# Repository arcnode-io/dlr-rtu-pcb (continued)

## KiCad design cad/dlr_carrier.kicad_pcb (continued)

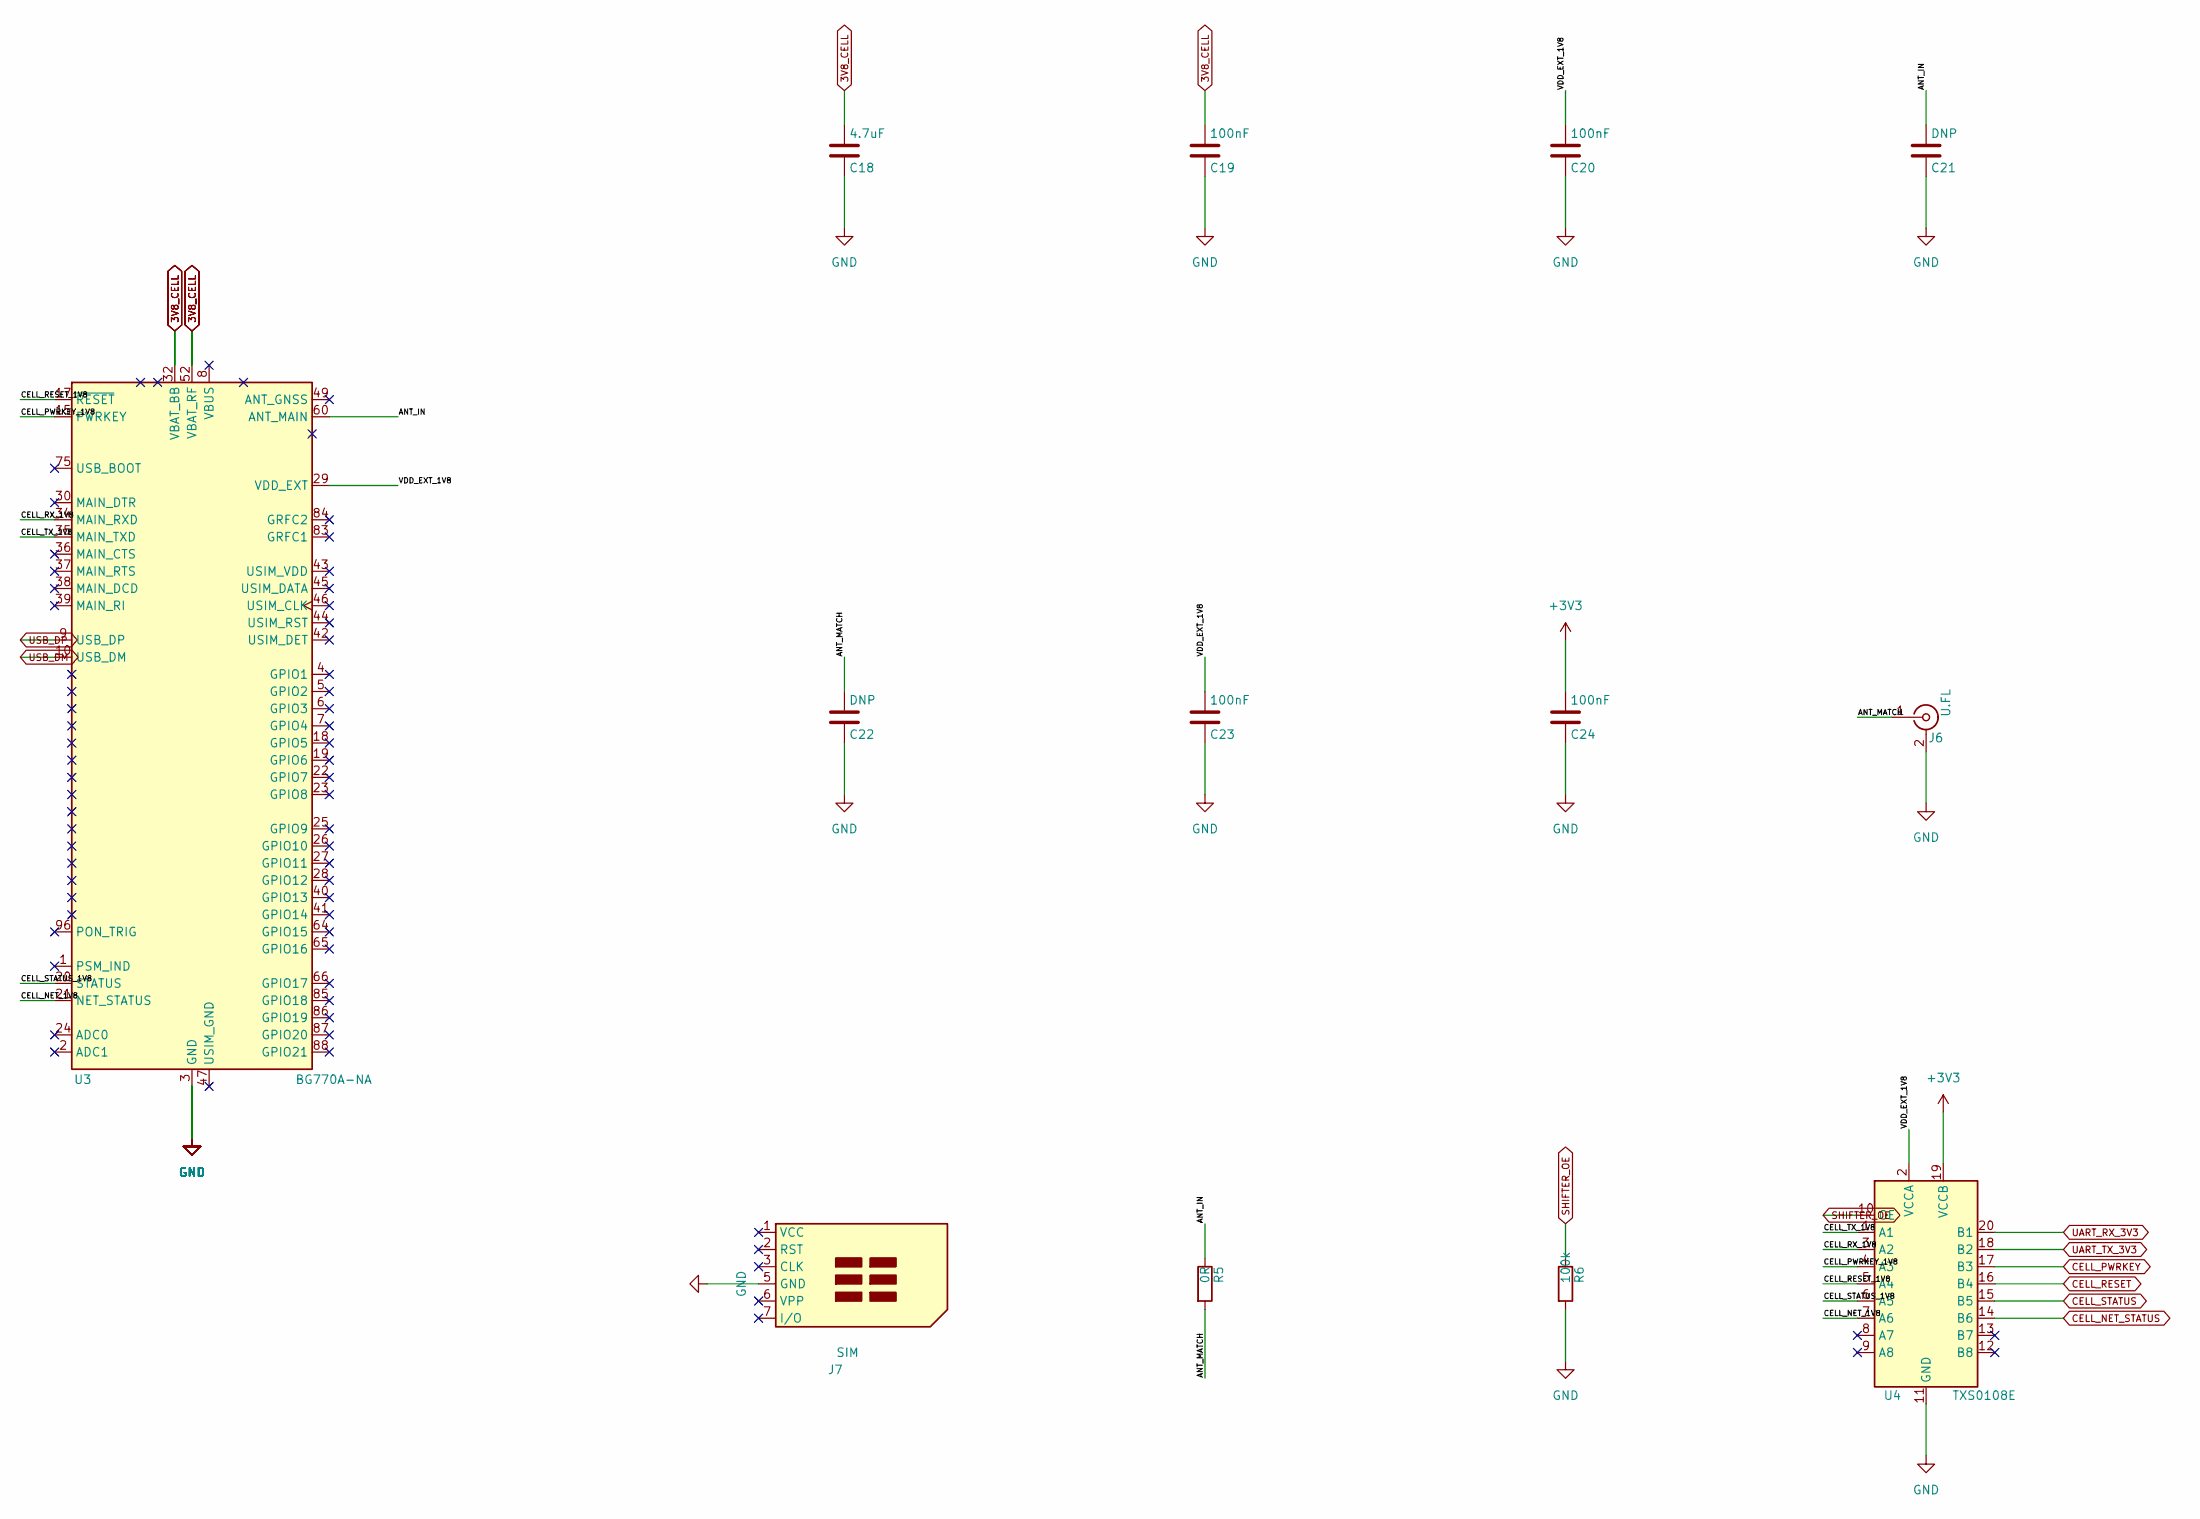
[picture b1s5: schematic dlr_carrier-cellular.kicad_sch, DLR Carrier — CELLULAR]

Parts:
C18: 4.7uF; C_0402_1005Metric
C19, C20, C23, C24: 100nF; C_0402_1005Metric
C21, C22: DNP; C_0402_1005Metric
J6: U.FL; U.FL_Hirose_U.FL-R-SMT-1_Vertical
J7: SIM; microSIM_JAE_SF53S006VCBR2000
R5: 0R; R_0402_1005Metric
R6: 100k; R_0402_1005Metric
U3: BG770A-NA; Quectel_BG95
U4: TXS0108E; TSSOP-20_4.4x6.5mm_P0.65mm

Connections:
3V3: C24.1, U4.19 (VCCB); also elsewhere on the board
3V8_CELL: C18.1, C19.1, U3.32 (VBAT_BB), U3.33 (VBAT_BB), U3.52 (VBAT_RF), U3.53 (VBAT_RF); also elsewhere on the board
ANT_IN: C21.1, R5.1, U3.60 (ANT_MAIN)
ANT_MATCH: C22.1, J6.1 (In), R5.2
CELL_NET_1V8: U3.21 (NET_STATUS), U4.7 (A6)
CELL_NET_STATUS: U4.14 (B6); also elsewhere on the board
CELL_PWRKEY: U4.17 (B3); also elsewhere on the board
CELL_PWRKEY_1V8: U3.15 (PWRKEY), U4.4 (A3)
CELL_RESET: U4.16 (B4); also elsewhere on the board
CELL_RESET_1V8: U3.17 (~RESET), U4.5 (A4)
CELL_RX_1V8: U3.34 (MAIN_RXD), U4.3 (A2)
CELL_STATUS: U4.15 (B5); also elsewhere on the board
CELL_STATUS_1V8: U3.20 (STATUS), U4.6 (A5)
CELL_TX_1V8: U3.35 (MAIN_TXD), U4.1 (A1)
GND: C18.2, C19.2, C20.2, C21.2, C22.2, C23.2, C24.2, J6.2 (Ext), J7.5 (GND), J7.SH, R6.2, U3.3 (GND), U3.31 (GND), U3.48 (GND), U3.50 (GND), U3.54 (GND), U3.55 (GND), U3.58 (GND), U3.59 (GND), U3.61 (GND), U3.62 (GND), U3.67 (GND), U3.68 (GND), U3.69 (GND), U3.70 (GND), U3.71 (GND), U3.72 (GND), U3.73 (GND), U3.74 (GND), U3.79 (GND), U3.80 (GND), U3.81 (GND), U3.82 (GND), U3.89 (GND), U3.90 (GND), U3.91 (GND), U3.100 (GND), U3.101 (GND), U3.102 (GND), U4.11 (GND); also elsewhere on the board
unnamed: J7.1 (VCC), U3.43 (USIM_VDD)
unnamed: J7.2 (RST), U3.44 (USIM_RST)
unnamed: J7.3 (CLK), U3.46 (USIM_CLK)
unnamed: J7.7 (I/O), U3.45 (USIM_DATA)
SHIFTER_OE: R6.1, U4.10 (OE); also elsewhere on the board
UART_RX_3V3: U4.20 (B1); also elsewhere on the board
UART_TX_3V3: U4.18 (B2); also elsewhere on the board
USB_DM: U3.10 (USB_DM); also elsewhere on the board
USB_DP: U3.9 (USB_DP); also elsewhere on the board
VDD_EXT_1V8: C20.1, C23.1, U3.29 (VDD_EXT), U4.2 (VCCA)

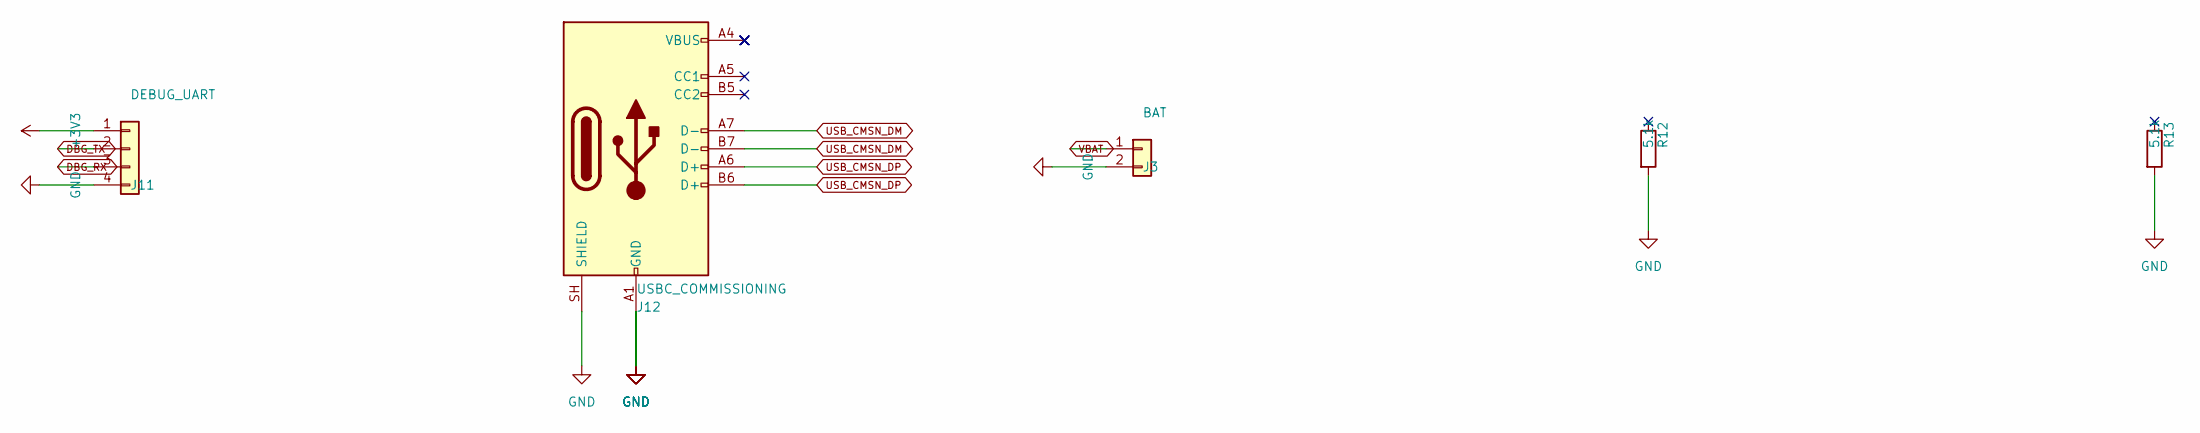
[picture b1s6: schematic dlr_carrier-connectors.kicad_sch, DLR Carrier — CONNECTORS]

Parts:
J3: BAT; TerminalBlock_Phoenix_MKDS-1,5-2-5.08_1x02_P5.08mm_Horizont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
J11: DEBUG_UART; PinHeader_1x04_P2.54mm_Vertical
J12: USBC_COMMISSIONING; USB_C_Receptacle_GCT_USB4085
R12, R13: 5.1k; R_0402_1005Metric

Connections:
3V3: J11.1; also elsewhere on the board
DBG_RX: J11.3; also elsewhere on the board
DBG_TX: J11.2; also elsewhere on the board
GND: J3.2, J11.4, J12.A1 (GND), J12.A12 (GND), J12.B1 (GND), J12.B12 (GND), J12.SH (SHIELD), R12.2, R13.2; also elsewhere on the board
unnamed: J12.A5 (CC1), R12.1
unnamed: J12.B5 (CC2), R13.1
USB_CMSN_DM: J12.A7 (D-), J12.B7 (D-); also elsewhere on the board
USB_CMSN_DP: J12.A6 (D+), J12.B6 (D+); also elsewhere on the board
VBAT: J3.1; also elsewhere on the board

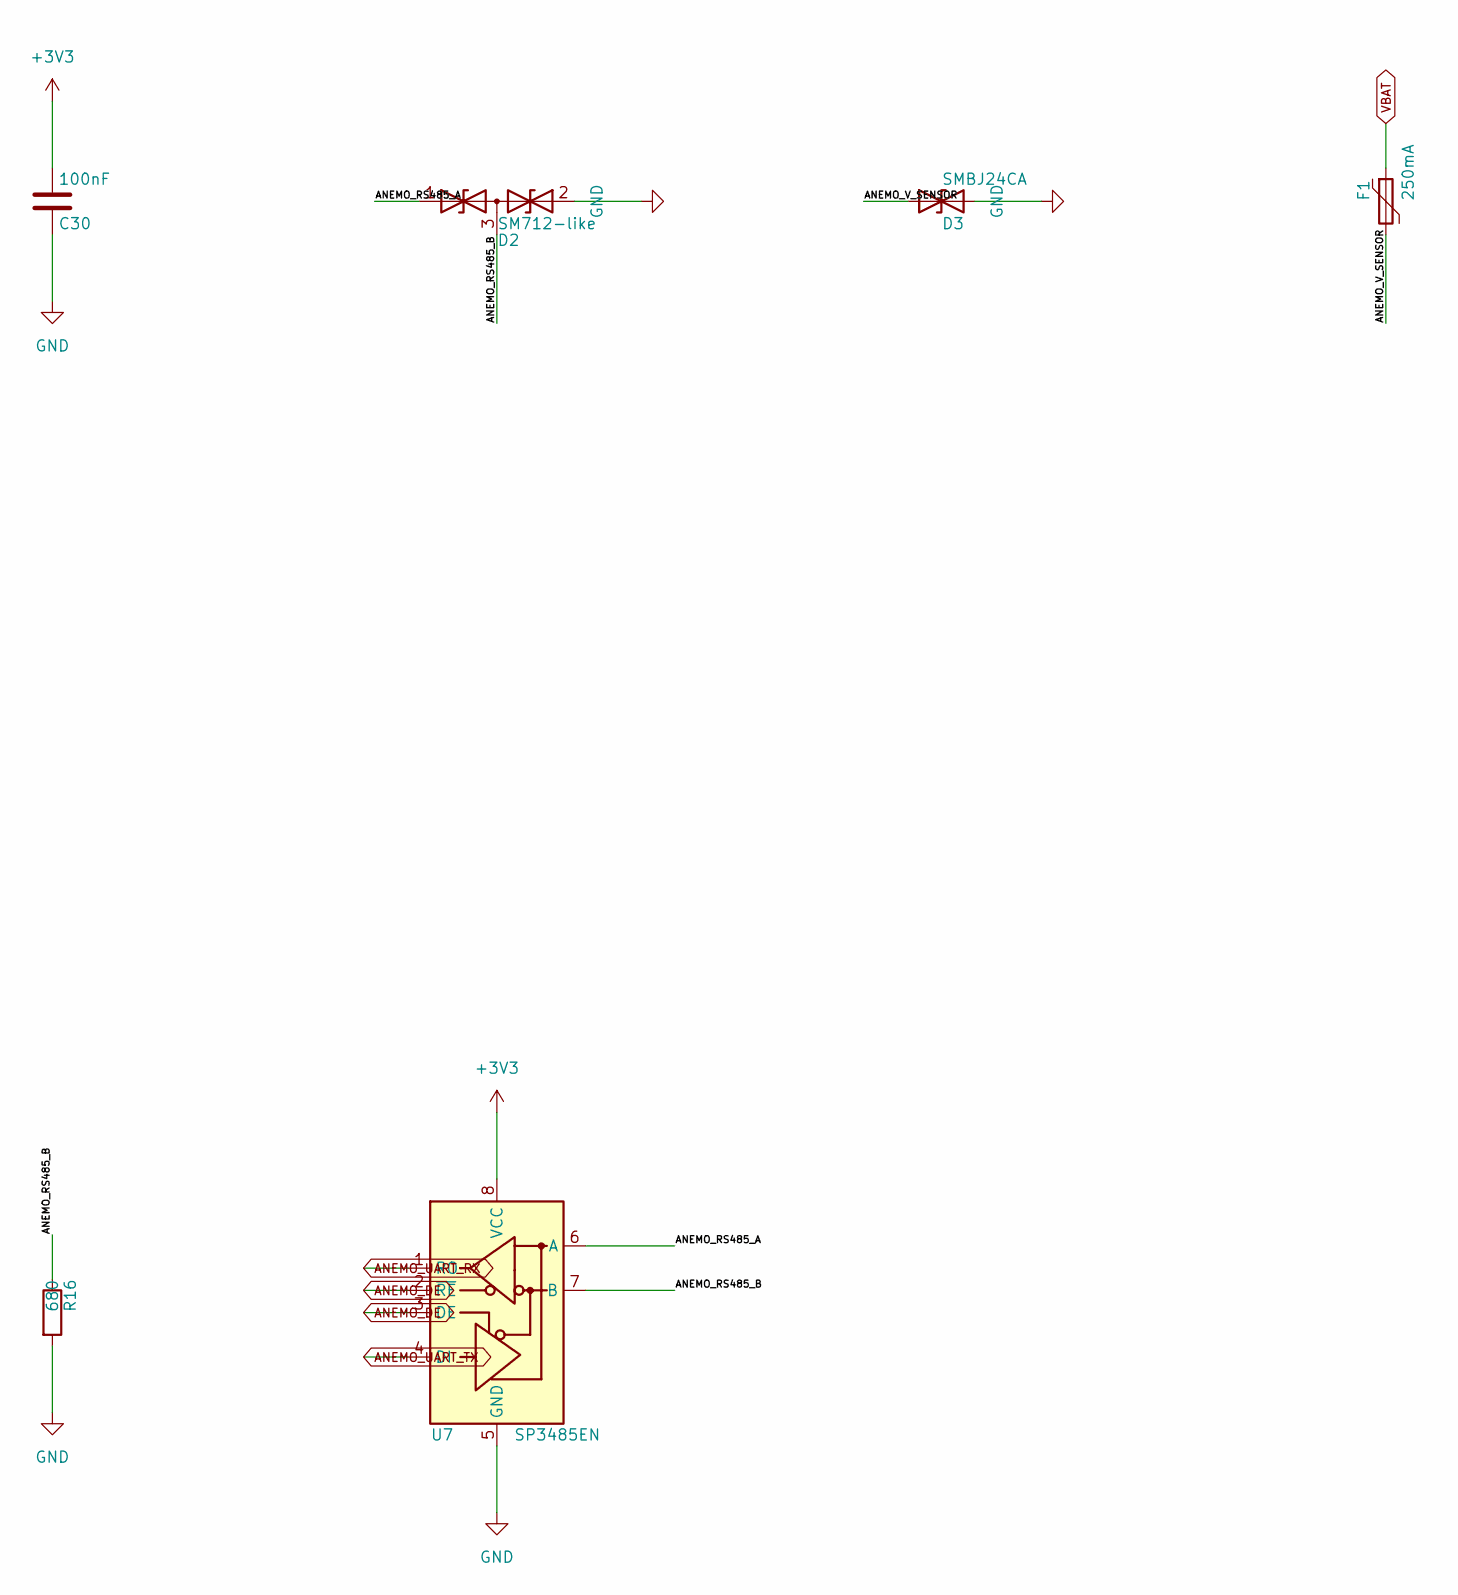
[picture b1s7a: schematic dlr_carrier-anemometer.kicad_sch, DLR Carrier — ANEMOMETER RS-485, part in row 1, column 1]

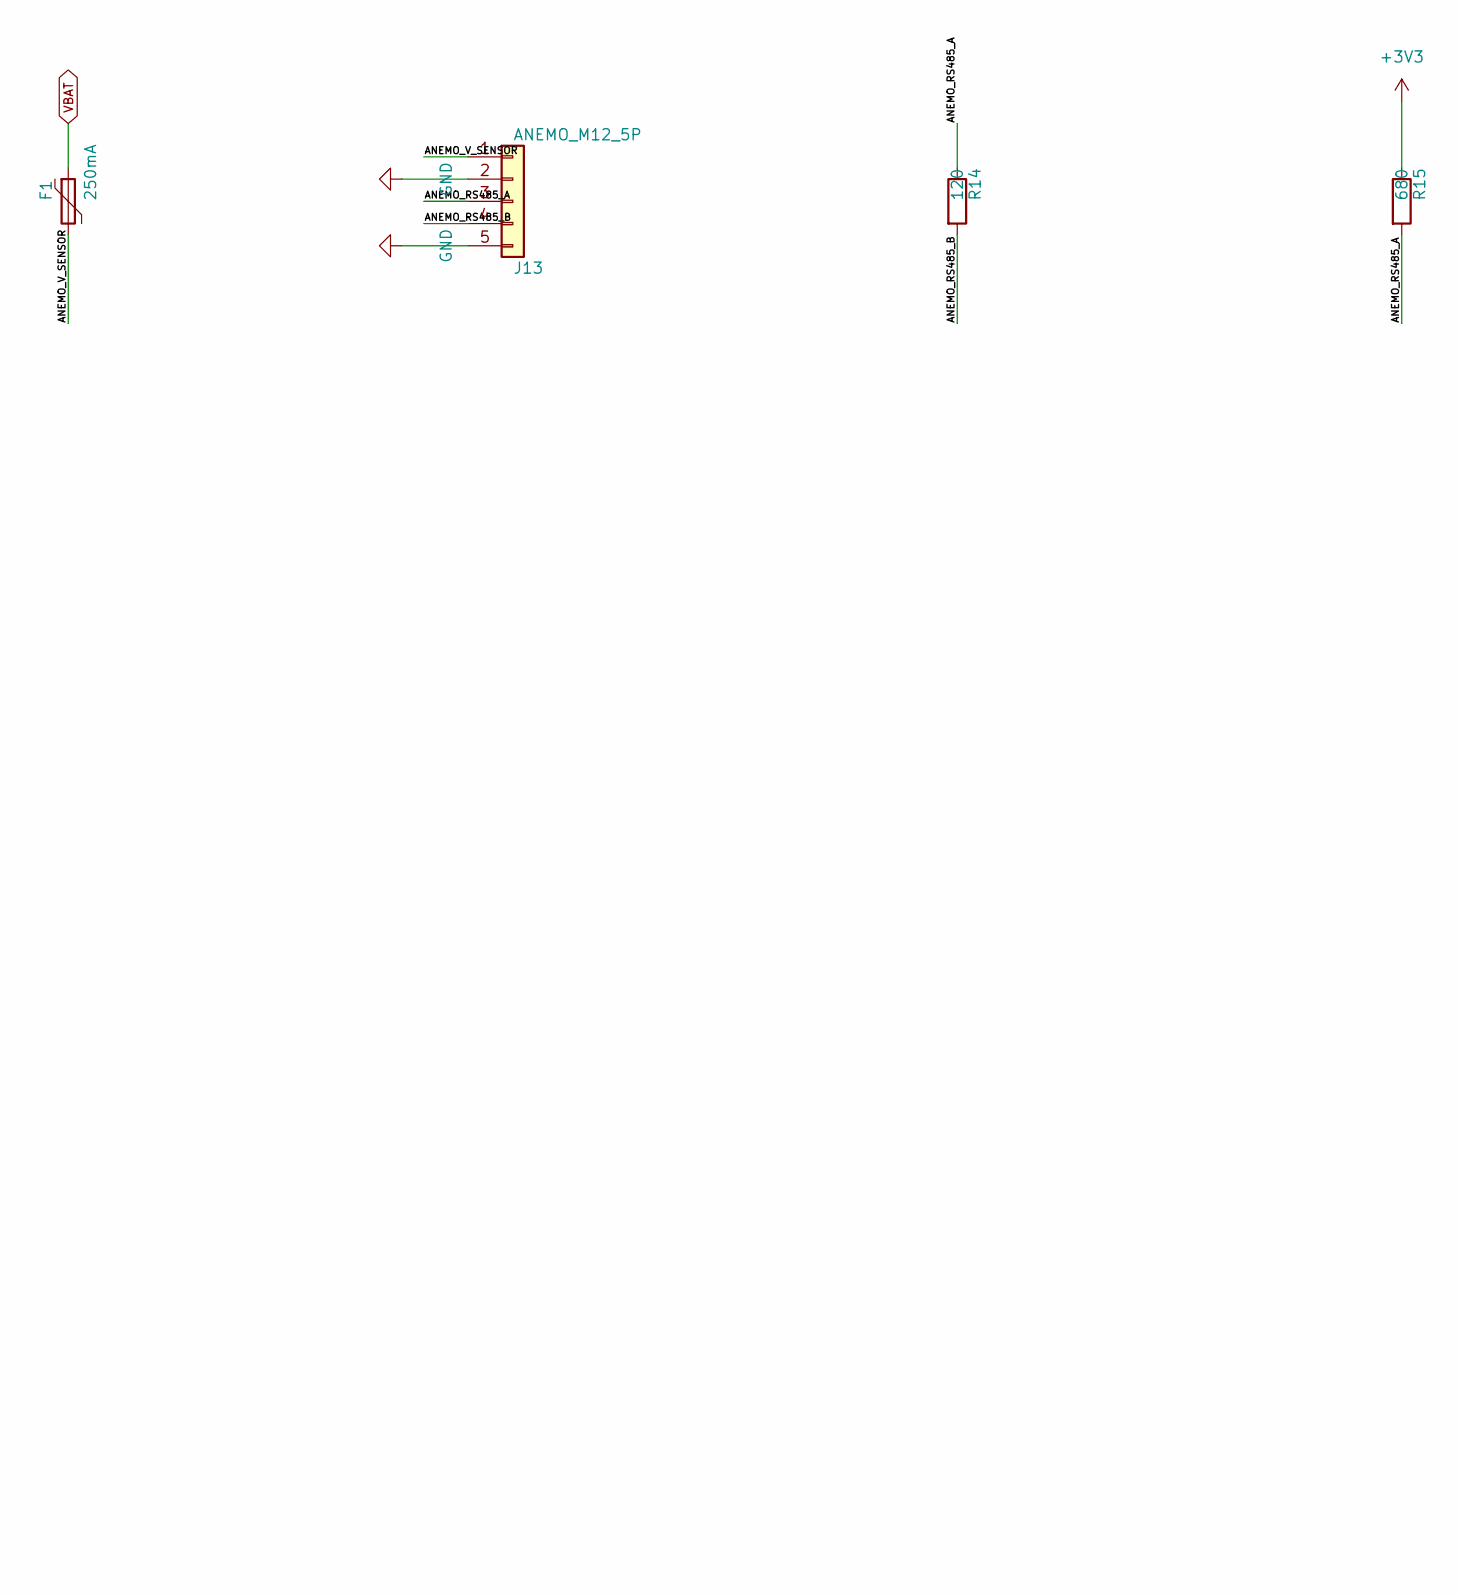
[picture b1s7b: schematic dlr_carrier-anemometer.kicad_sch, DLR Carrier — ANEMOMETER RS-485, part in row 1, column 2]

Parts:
C30: 100nF; C_0402_1005Metric
D2: SM712-like; SOT-23
D3: SMBJ24CA; D_SMB
F1: 250mA; R_1206_3216Metric
J13: ANEMO_M12_5P; PinHeader_1x05_P2.54mm_Vertical
R14: 120; R_0402_1005Metric
R15, R16: 680; R_0402_1005Metric
U7: SP3485EN; SOIC-8_3.9x4.9mm_P1.27mm

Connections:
3V3: C30.1, R15.1, U7.8 (VCC); also elsewhere on the board
ANEMO_DE: U7.2 (~RE), U7.3 (DE); also elsewhere on the board
ANEMO_RS485_A: D2.1 (A1), J13.3, R14.1, R15.2, U7.6 (A)
ANEMO_RS485_B: D2.3 (common), J13.4, R14.2, R16.1, U7.7 (B)
ANEMO_UART_RX: U7.1 (RO); also elsewhere on the board
ANEMO_UART_TX: U7.4 (DI); also elsewhere on the board
ANEMO_V_SENSOR: D3.1 (A1), F1.2, J13.1
GND: C30.2, D2.2 (A2), D3.2 (A2), J13.2, J13.5, R16.2, U7.5 (GND); also elsewhere on the board
VBAT: F1.1; also elsewhere on the board

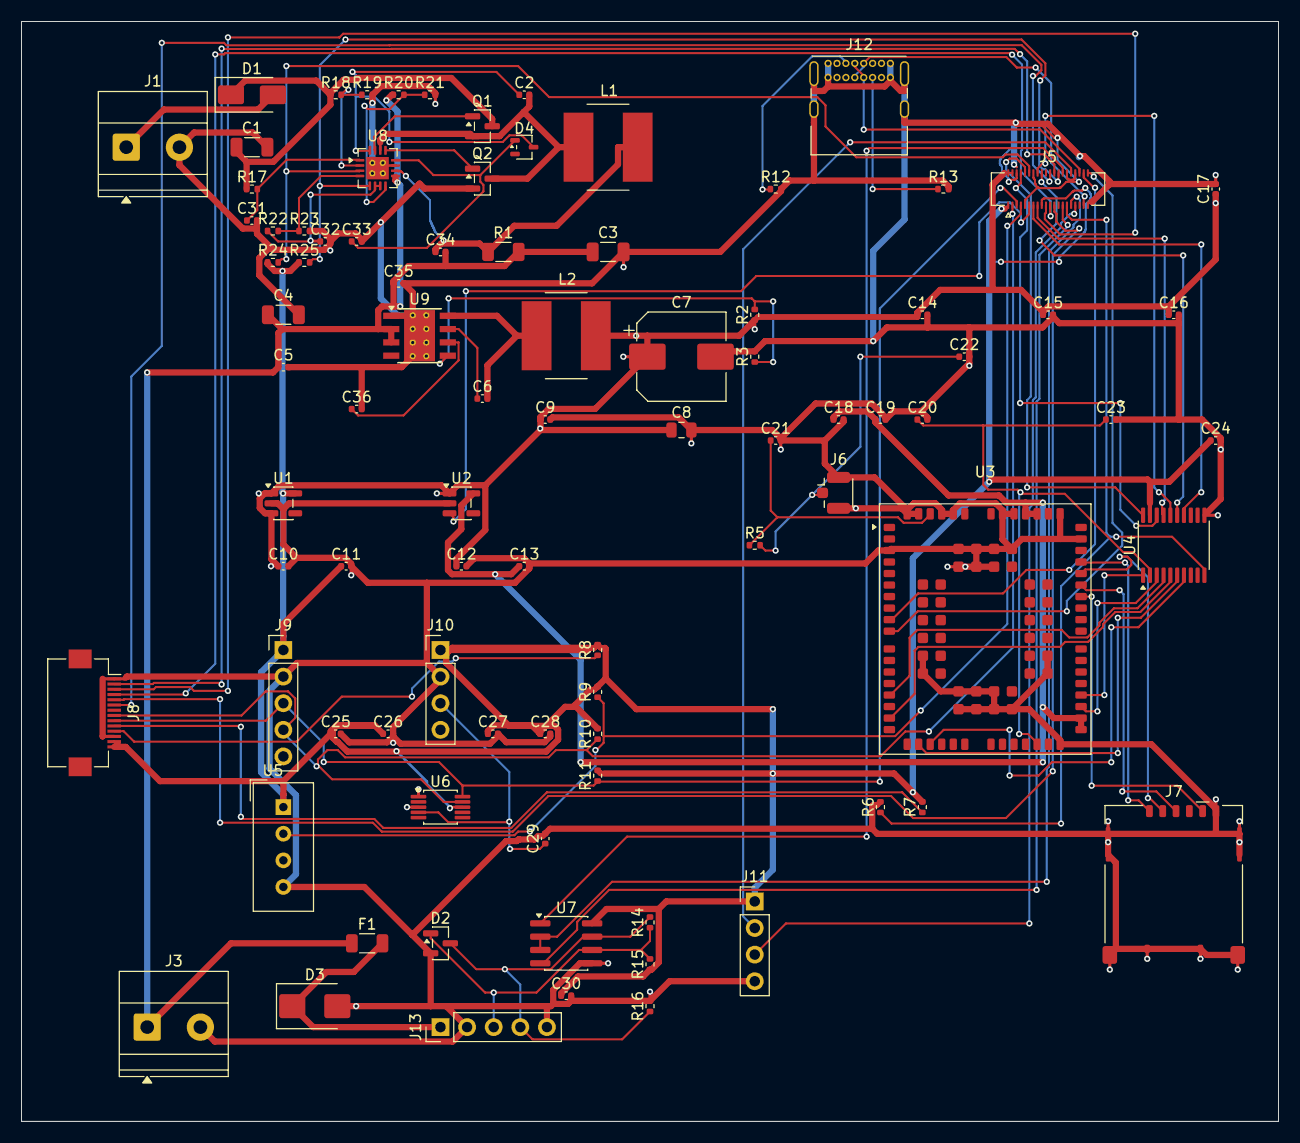
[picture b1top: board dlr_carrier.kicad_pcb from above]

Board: 4 copper layers, 120.0 x 105.0 mm, 89 parts (0 on the bottom side), 70 nets.

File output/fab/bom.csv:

"Designator","Comment","Footprint","Quantity"
"C1,C3","22uF","Capacitor_SMD:C_1206_3216Metric","2"
"C2,C6,C9,C14-C17,C19,C20,C23-C28,C30,C34,C35","100nF","Capacitor_SMD:C_0402_1005Metric","18"
"C4","10uF","Capacitor_SMD:C_1206_3216Metric","1"
"C5","220nF","Capacitor_SMD:C_0402_1005Metric","1"
"C7","470uF","Capacitor_SMD:CP_Elec_8x10","1"
"C8","22uF","Capacitor_SMD:C_0805_2012Metric","1"
"C10-C13,C31-C33,C36","1uF","Capacitor_SMD:C_0402_1005Metric","8"
"C18","4.7uF","Capacitor_SMD:C_0402_1005Metric","1"
"C21,C22","DNP","Capacitor_SMD:C_0402_1005Metric","2"
"C29","10nF","Capacitor_SMD:C_0402_1005Metric","1"
"D1","SS34","Diode_SMD:D_SMA","1"
"D2","SM712-like","Package_TO_SOT_SMD:SOT-23","1"
"D3","SMBJ24CA","Diode_SMD:D_SMB","1"
"D4","BAT54W","Package_TO_SOT_SMD:SOT-323_SC-70","1"
"F1","250mA","Resistor_SMD:R_1206_3216Metric","1"
"J1","PV_IN","TerminalBlock_Phoenix:TerminalBlock_Phoenix_MKDS-1,5-2-5.08_1x02_P5.08mm_Horizontal","1"
"J3","BAT","TerminalBlock_Phoenix:TerminalBlock_Phoenix_MKDS-1,5-2-5.08_1x02_P5.08mm_Horizontal","1"
"J5","CM4_J2","Connector_Hirose_DF40:Hirose_DF40HC(3.0)-40DS-0.4V_2x20_P0.4mm","1"
"J6","U.FL","Connector_Coaxial:U.FL_Hirose_U.FL-R-SMT-1_Vertical","1"
"J7","SIM","Connector_Card:microSIM_JAE_SF53S006VCBR2000","1"
"J8","FLIR_LEPTON_FFC","Connector_FFC-FPC:Hirose_FH12-14S-0.5SH_1x14-1MP_P0.50mm_Horizontal","1"
"J9","SI1145","Connector_PinHeader_2.54mm:PinHeader_1x05_P2.54mm_Vertical","1"
"J10","YL-83","Connector_PinHeader_2.54mm:PinHeader_1x04_P2.54mm_Vertical","1"
"J11","DEBUG_UART","Connector_PinHeader_2.54mm:PinHeader_1x04_P2.54mm_Vertical","1"
"J12","USBC_COMMISSIONING","Connector_USB:USB_C_Receptacle_GCT_USB4085","1"
"J13","ANEMO_M12_5P","Connector_PinHeader_2.54mm:PinHeader_1x05_P2.54mm_Vertical","1"
"L1","6.8uH","Inductor_SMD:L_Bourns_SRN8040TA","1"
"L2","10uH","Inductor_SMD:L_Bourns_SRN8040TA","1"
"Q1,Q2","DMN4035L-7","Package_TO_SOT_SMD:SOT-23","2"
"R1","20m","Resistor_SMD:R_1206_3216Metric","1"
"R2,R6","100k","Resistor_SMD:R_0402_1005Metric","2"
"R3","24.9k","Resistor_SMD:R_0402_1005Metric","1"
"R5","0R","Resistor_SMD:R_0402_1005Metric","1"
"R7-R9,R19,R22,R24,R25","10k","Resistor_SMD:R_0402_1005Metric","7"
"R10,R11","2.2k","Resistor_SMD:R_0402_1005Metric","2"
"R12,R13","5.1k","Resistor_SMD:R_0402_1005Metric","2"
"R14","120","Resistor_SMD:R_0402_1005Metric","1"
"R15,R16","680","Resistor_SMD:R_0402_1005Metric","2"
"R17","10","Resistor_SMD:R_0402_1005Metric","1"
"R18","130k","Resistor_SMD:R_0402_1005Metric","1"
"R20","297k","Resistor_SMD:R_0402_1005Metric","1"
"R21","49.9k","Resistor_SMD:R_0402_1005Metric","1"
"R23","15k","Resistor_SMD:R_0402_1005Metric","1"
"U1","AP2112K-3.3","Package_TO_SOT_SMD:SOT-23-5","1"
"U2","LP5907MFX-3.8","Package_TO_SOT_SMD:SOT-23-5","1"
"U3","BG770A-NA","RF_GSM:Quectel_BG95","1"
"U4","TXS0108E","Package_SO:TSSOP-20_4.4x6.5mm_P0.65mm","1"
"U5","DHT22","Sensor:Aosong_DHT11_5.5x12.0_P2.54mm","1"
"U6","ADS1115","Package_SO:MSOP-10_3x3mm_P0.5mm","1"
"U7","SP3485EN","Package_SO:SOIC-8_3.9x4.9mm_P1.27mm","1"
"U8","BQ24650RVAR","Package_DFN_QFN:Texas_RVA_VQFN-16-1EP_3.5x3.5mm_P0.5mm_EP2.14x2.14mm_ThermalVias","1"
"U9","LMR33630ADDA","Package_SO:Texas_HSOP-8-1EP_3.9x4.9mm_P1.27mm_ThermalVias","1"

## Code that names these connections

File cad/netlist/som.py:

"""CM4 SoM connector — represented as 40-pin Pi GPIO header equivalent.

Real CM4 has 2x DF40-100 board-to-board connectors (not in default kicad libs).
For netlist-stage we use Conn_02x20_Odd_Even (40 pins) with Pi-standard pinout —
sufficient for connectivity verification. Final layout uses a custom DF40-100 footprint.
"""

import skidl


def build_cm4(
    v5_in: skidl.Net,
    v3v3: skidl.Net,
    gnd: skidl.Net,
    sda: skidl.Net,
    scl: skidl.Net,
    spi_mosi: skidl.Net,
    spi_miso: skidl.Net,
    spi_sck: skidl.Net,
    spi_ce0: skidl.Net,
    uart_tx: skidl.Net,
    uart_rx: skidl.Net,
    gpio4: skidl.Net,
    gpio25: skidl.Net,
    cell_en: skidl.Net,
    usb_dp: skidl.Net,
    usb_dm: skidl.Net,
    cmsn_dp: skidl.Net,
    cmsn_dm: skidl.Net,
    pwrkey: skidl.Net,
    reset_n: skidl.Net,
    status: skidl.Net,
    net_status: skidl.Net,
    shifter_oe: skidl.Net,
    dbg_tx: skidl.Net,
    dbg_rx: skidl.Net,
    anemo_uart_tx: skidl.Net,
    anemo_uart_rx: skidl.Net,
    anemo_de_n: skidl.Net,
    chg_stat1: skidl.Net,
    chg_stat2: skidl.Net,
) -> None:
    """Wire CM4 J2 (GPIO/UART/I2C/SPI/USB2) to the carrier.

    Pin numbers follow Pi 40-pin GPIO header convention. CM4 J2 DF40 has
    different physical pin numbers but the same signal set; final layout
    requires the custom DF40-100 footprint.
    """
    j_cm4 = skidl.Part(
        "Connector_Generic",
        "Conn_02x20_Odd_Even",
        ref="J5",
        footprint="Connector_Hirose_DF40:Hirose_DF40HC(3.0)-40DS-0.4V_2x20_P0.4mm",
    )
    j_cm4.value = "CM4_J2"

    # Power rails (Pi GPIO header standard)
    v3v3 += j_cm4[1]
    v5_in += j_cm4[2]
    v5_in += j_cm4[4]
    v3v3 += j_cm4[17]
    for pin in (6, 9, 14, 20, 25, 30, 34, 39):
        gnd += j_cm4[pin]

    # I2C1 (sensors bus)
    sda += j_cm4[3]  # GPIO2
    scl += j_cm4[5]  # GPIO3

    # 1-wire DHT22 + Lepton VSYNC
    gpio4 += j_cm4[7]  # GPIO4
    gpio25 += j_cm4[22]  # GPIO25

    # UART0 to BG770A (via TXS0108E)
    uart_tx += j_cm4[8]  # GPIO14 / TXD0
    uart_rx += j_cm4[10]  # GPIO15 / RXD0

    # Cellular interface controls
    cell_en += j_cm4[11]  # GPIO17 — LP5907 EN
    net_status += j_cm4[13]  # GPIO27 — BG770A NET_STATUS (input)
    pwrkey += j_cm4[15]  # GPIO22 — BG770A PWRKEY
    reset_n += j_cm4[16]  # GPIO23 — BG770A ~{RESET}
    status += j_cm4[18]  # GPIO24 — BG770A STATUS (input)
    shifter_oe += j_cm4[29]  # GPIO5 — TXS0108E OE

    # Debug UART (UART4 on GPIO12/13 — CM4 secondary UART)
    dbg_tx += j_cm4[32]  # GPIO12 / TXD4
    dbg_rx += j_cm4[33]  # GPIO13 / RXD4

    # SPI0 — FLIR Lepton
    spi_mosi += j_cm4[19]  # GPIO10 / MOSI
    spi_miso += j_cm4[21]  # GPIO9 / MISO
    spi_sck += j_cm4[23]  # GPIO11 / SCLK
    spi_ce0 += j_cm4[24]  # GPIO8 / CE0

    # UART2 to anemometer RS-485 transceiver (dtoverlay=uart2 maps to GPIO0/1)
    anemo_uart_tx += j_cm4[27]  # GPIO0 / TXD2
    anemo_uart_rx += j_cm4[28]  # GPIO1 / RXD2
    anemo_de_n += j_cm4[31]  # GPIO6 — SP3485EN DE/~RE direction control

    # BQ24650 charge status (open drain, pulled up to 3V3 in charger.py) — telemetry
    chg_stat1 += j_cm4[12]  # GPIO18 — STAT1 low = charging
    chg_stat2 += j_cm4[26]  # GPIO7 — STAT2 low = charge complete

    # USB2 to BG770A — placeholder pins (real CM4 USB lives on J1, not GPIO header)
    usb_dp += j_cm4[38]
    usb_dm += j_cm4[40]

    # USB2 OTG → commissioning USB-C port (ADR-013)
    # Placeholder pins; real CM4 J1 has a separate OTG pair, exposed via the
    # custom DF40-100 footprint at PCB layout time.
    cmsn_dp += j_cm4[36]
    cmsn_dm += j_cm4[37]

    # 4x 100nF decoupling near connector
    for ref in ("C14", "C15", "C16", "C17"):
        c = skidl.Part(
            "Device",
            "C",
            ref=ref,
            value="100nF",
            footprint="Capacitor_SMD:C_0402_1005Metric",
        )
        v5_in += c[1]
        gnd += c[2]

    # Truly unused pins. Reason: listing a pin here that is wired above merges the
    # NC_ net into the real one and SKiDL may keep the NC_ name (ANEMO_DE became NC_CM4_31)
    skidl.Net("NC_CM4_35") & j_cm4[35]
